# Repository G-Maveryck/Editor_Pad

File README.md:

# Editor_Pad
 Pad for professional editors, for easing the edit process.

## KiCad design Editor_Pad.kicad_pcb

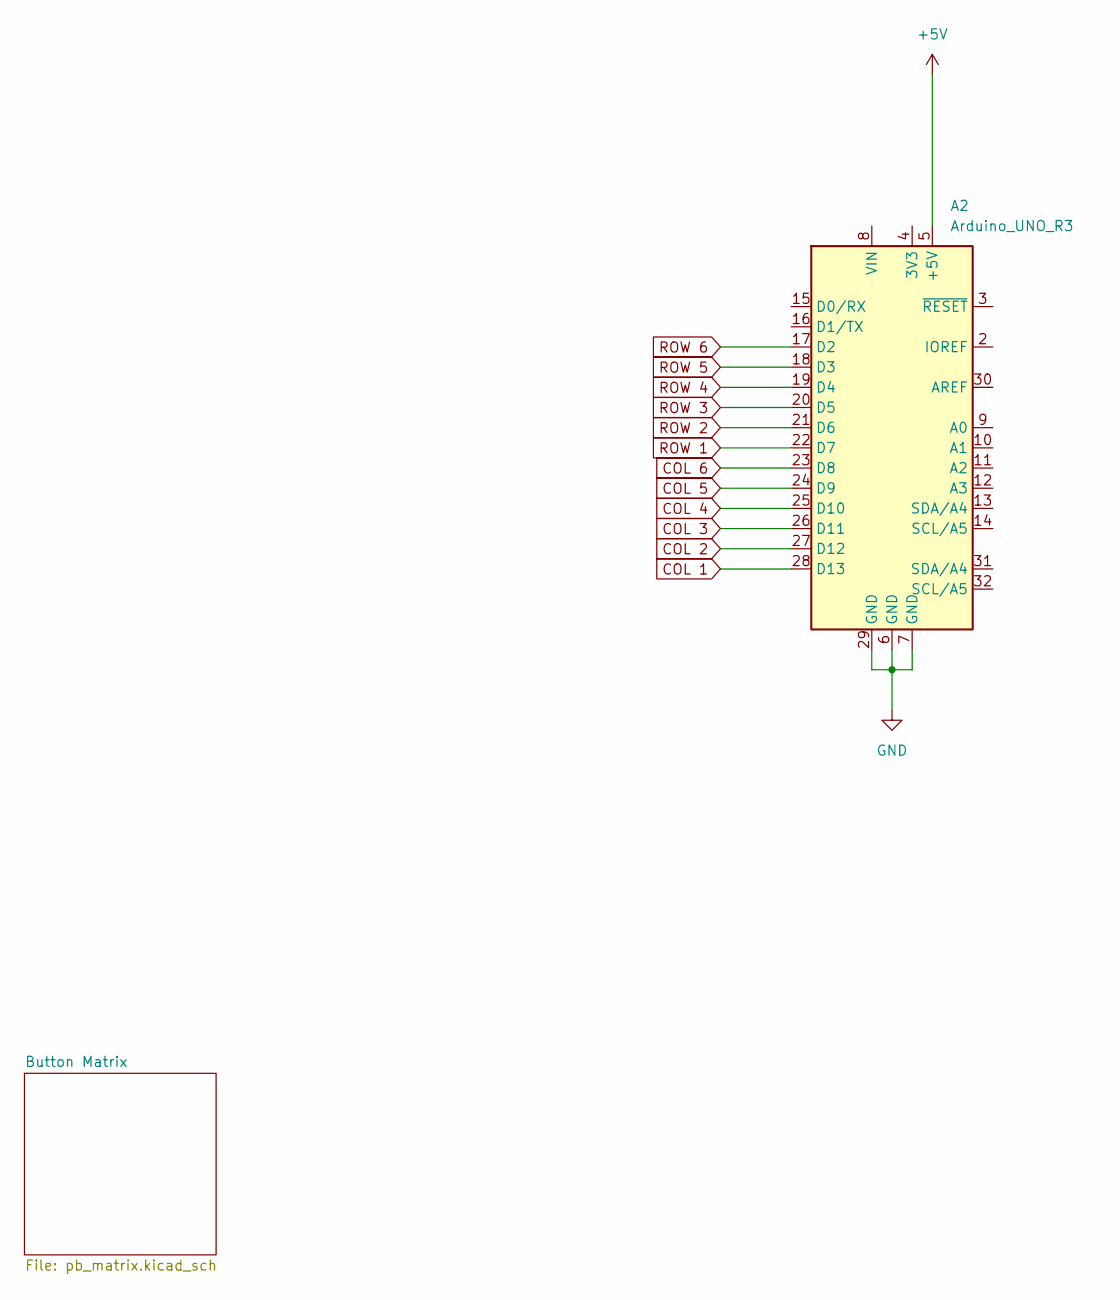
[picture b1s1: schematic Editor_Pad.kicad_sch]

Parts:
A2: Arduino_UNO_R3

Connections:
+5V: A2.5 (+5V); also elsewhere on the board
COL 1: A2.28 (D13); also elsewhere on the board
COL 2: A2.27 (D12); also elsewhere on the board
COL 3: A2.26 (D11); also elsewhere on the board
COL 4: A2.25 (D10); also elsewhere on the board
COL 5: A2.24 (D9); also elsewhere on the board
COL 6: A2.23 (D8); also elsewhere on the board
GND: A2.6 (GND), A2.7 (GND), A2.29 (GND); also elsewhere on the board
ROW 1: A2.22 (D7); also elsewhere on the board
ROW 2: A2.21 (D6); also elsewhere on the board
ROW 3: A2.20 (D5); also elsewhere on the board
ROW 4: A2.19 (D4); also elsewhere on the board
ROW 5: A2.18 (D3); also elsewhere on the board
ROW 6: A2.17 (D2); also elsewhere on the board

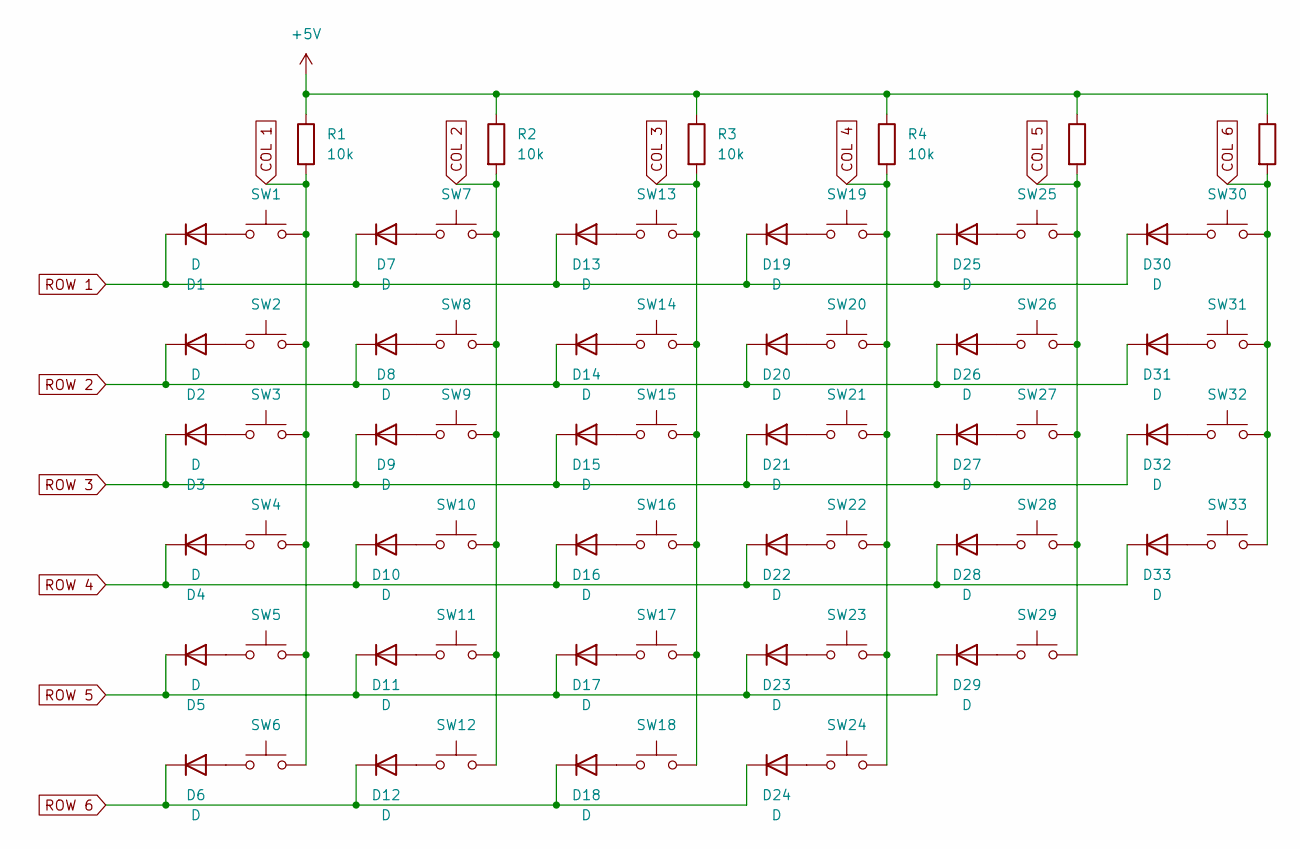
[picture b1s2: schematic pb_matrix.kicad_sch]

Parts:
D1, D2, D3, D4, D5, D6, D7, D8, D9, D10, D11, D12, D13, D14, D15, D16, D17, D18, D19, D20, D21, D22, D23, D24, D25, D26, D27, D28, D29, D30, D31, D32, D33: D; D_0603_1608Metric_Pad1.05x0.95mm_HandSolder
R1, R2, R3, R4, R5, R6: 10k; R_0603_1608Metric
SW1, SW2, SW3, SW4, SW5, SW6, SW7, SW8, SW9, SW10, SW11, SW12, SW13, SW14, SW15, SW16, SW17, SW18, SW19, SW20, SW21, SW22, SW23, SW24, SW29: SW_Push; SW_Cherry_MX_PCB_1.00u
SW25, SW26, SW27, SW28, SW30, SW31, SW32, SW33: SW_Push; SW_PUSH_6mm

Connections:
+5V: R1.1, R2.1, R3.1, R4.1, R5.1, R6.1; also elsewhere on the board
COL 1: R1.2, SW1.2, SW2.2, SW3.2, SW4.2, SW5.2, SW6.2; also elsewhere on the board
COL 2: R2.2, SW7.2, SW8.2, SW9.2, SW10.2, SW11.2, SW12.2; also elsewhere on the board
COL 3: R3.2, SW13.2, SW14.2, SW15.2, SW16.2, SW17.2, SW18.2; also elsewhere on the board
COL 4: R4.2, SW19.2, SW20.2, SW21.2, SW22.2, SW23.2, SW24.2; also elsewhere on the board
COL 5: R5.2, SW25.2, SW26.2, SW27.2, SW28.2, SW29.2; also elsewhere on the board
COL 6: R6.2, SW30.2, SW31.2, SW32.2, SW33.2; also elsewhere on the board
unnamed: D1.2 (A), SW1.1
unnamed: D2.2 (A), SW2.1
unnamed: D3.2 (A), SW3.1
unnamed: D4.2 (A), SW4.1
unnamed: D5.2 (A), SW5.1
unnamed: D6.2 (A), SW6.1
unnamed: D7.2 (A), SW7.1
unnamed: D8.2 (A), SW8.1
unnamed: D9.2 (A), SW9.1
unnamed: D10.2 (A), SW10.1
unnamed: D11.2 (A), SW11.1
unnamed: D12.2 (A), SW12.1
unnamed: D13.2 (A), SW13.1
unnamed: D14.2 (A), SW14.1
unnamed: D15.2 (A), SW15.1
unnamed: D16.2 (A), SW16.1
unnamed: D17.2 (A), SW17.1
unnamed: D18.2 (A), SW18.1
unnamed: D19.2 (A), SW19.1
unnamed: D20.2 (A), SW20.1
unnamed: D21.2 (A), SW21.1
unnamed: D22.2 (A), SW22.1
unnamed: D23.2 (A), SW23.1
unnamed: D24.2 (A), SW24.1
unnamed: D25.2 (A), SW25.1
unnamed: D26.2 (A), SW26.1
unnamed: D27.2 (A), SW27.1
unnamed: D28.2 (A), SW28.1
unnamed: D29.2 (A), SW29.1
unnamed: D30.2 (A), SW30.1
unnamed: D31.2 (A), SW31.1
unnamed: D32.2 (A), SW32.1
unnamed: D33.2 (A), SW33.1
ROW 1: D1.1 (K), D7.1 (K), D13.1 (K), D19.1 (K), D25.1 (K), D30.1 (K); also elsewhere on the board
ROW 2: D2.1 (K), D8.1 (K), D14.1 (K), D20.1 (K), D26.1 (K), D31.1 (K); also elsewhere on the board
ROW 3: D3.1 (K), D9.1 (K), D15.1 (K), D21.1 (K), D27.1 (K), D32.1 (K); also elsewhere on the board
ROW 4: D4.1 (K), D10.1 (K), D16.1 (K), D22.1 (K), D28.1 (K), D33.1 (K); also elsewhere on the board
ROW 5: D5.1 (K), D11.1 (K), D17.1 (K), D23.1 (K), D29.1 (K); also elsewhere on the board
ROW 6: D6.1 (K), D12.1 (K), D18.1 (K), D24.1 (K); also elsewhere on the board

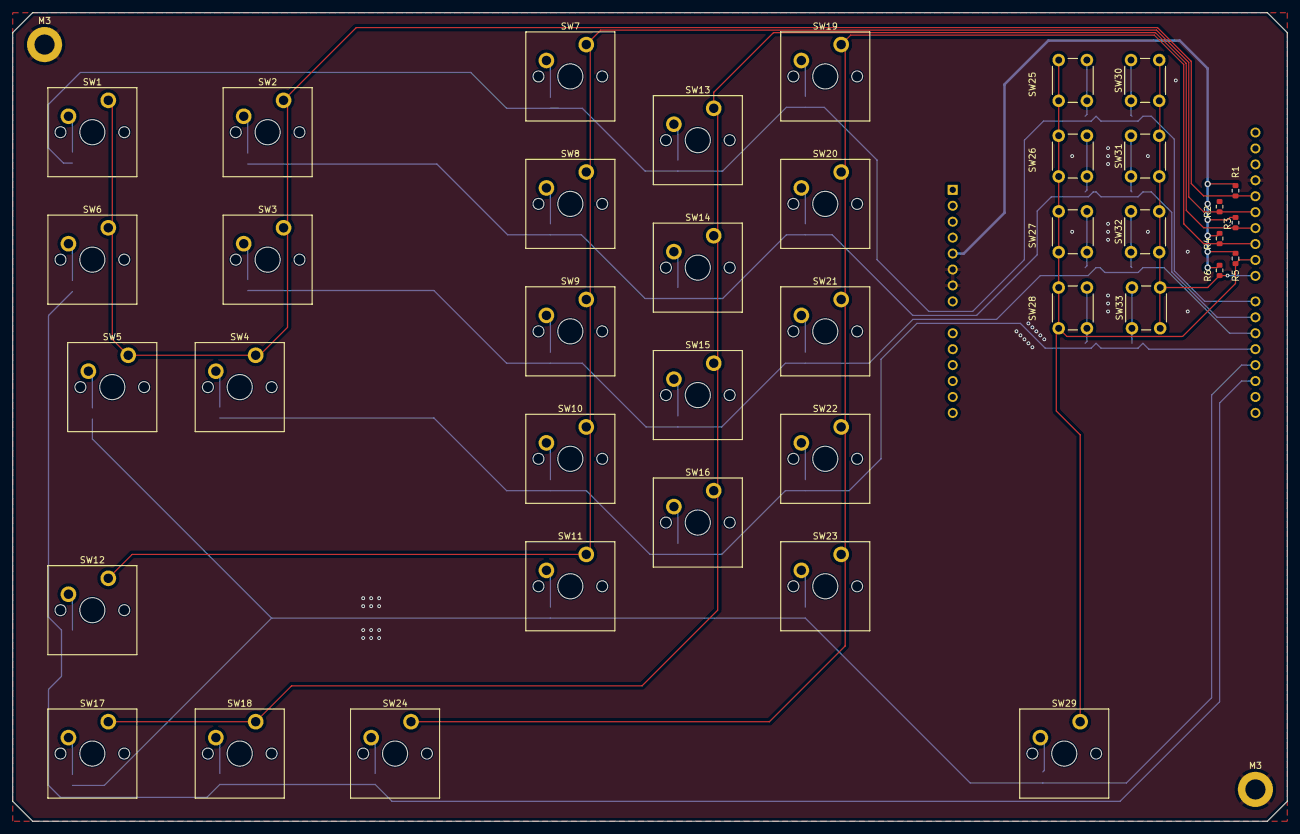
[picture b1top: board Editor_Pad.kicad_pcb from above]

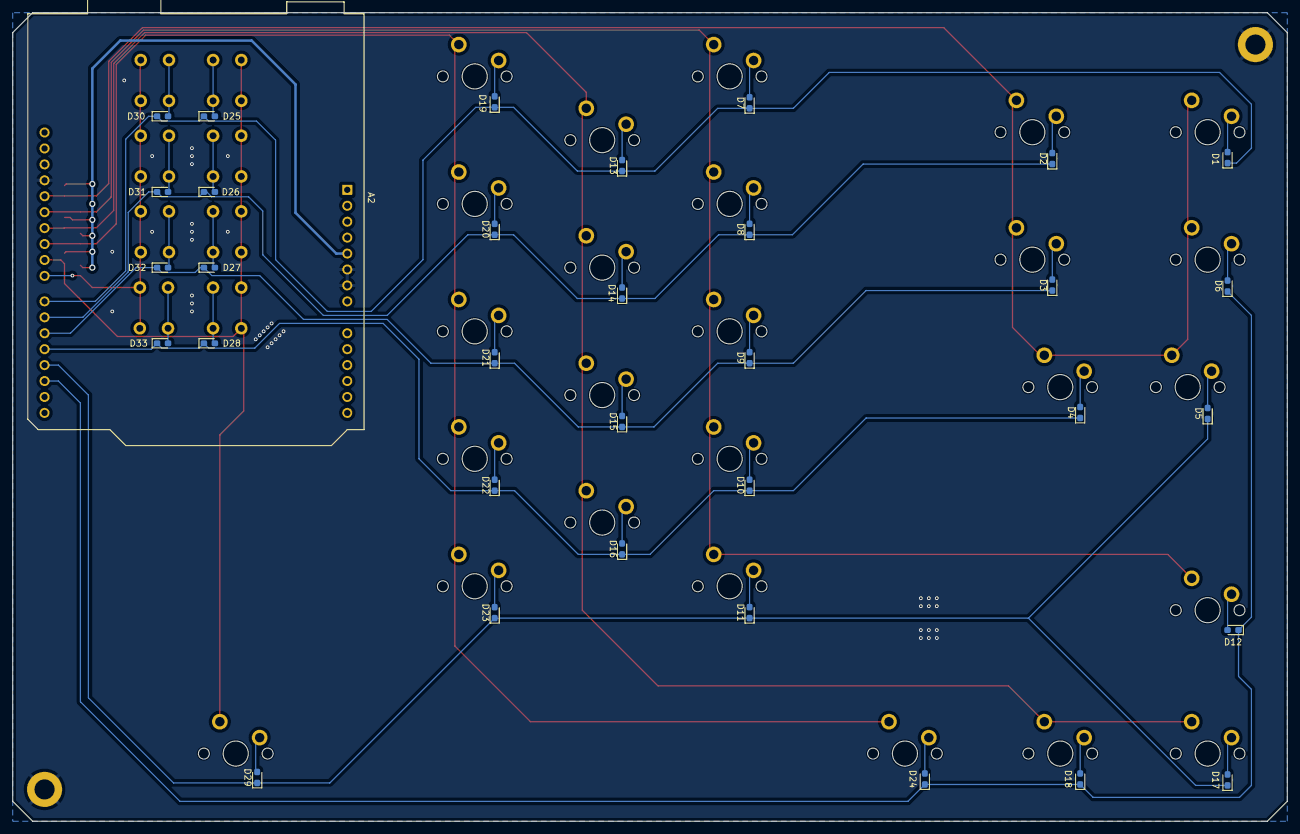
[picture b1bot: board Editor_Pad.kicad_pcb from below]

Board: 2 copper layers, 203.2 x 128.9 mm, 75 parts (34 on the bottom side), 47 nets.

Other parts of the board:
M3, M3#2: MountingHole_3.2mm_M3_DIN965_Pad

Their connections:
GND: M3.1, M3#2.1; also elsewhere on the board

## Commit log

2024-05-03 Working on a proper routing
2024-09-26 Slightly modified
